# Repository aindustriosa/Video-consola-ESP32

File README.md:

# Videoconsola ESP32

Unha videoconsola portátil feita por nós, e un SDK para aprender a programar
os teus propios xogos nela.

## Que leva

- **XIAO ESP32-C3** (o cerebro)
- Pantalla a cor **ILI9341 de 2,4"** (240 x 320 puntos)
- Cruceta, botóns **A**, **B** e **MENU**
- Zumbador para facer sons
- Batería **LiPo** que se carga polo USB-C

## Que hai neste repositorio

| Carpeta | Contido |
|---|---|
| `lib/VideoConsola/` | O SDK: a librería para programar a consola |
| `lib/VideoConsola/examples/` | Exemplos, do máis sinxelo ao máis completo |
| `xogo/` | Aquí vai o teu programa |
| `docs/` | [Primeiros pasos](docs/primeiros-pasos.md) e [referencia do SDK](docs/referencia.md) |
| `hardware/` | [PCB (KiCad), esquema, lista de materiais e carcasa 3D](hardware/README.md) |

## Un programa en 10 liñas

```cpp
#include <VideoConsola.h>

void setup() {
  consola.iniciar();
  pantalla.texto_centrado("Ola, mundo!", 150, AMARELO);
}

void loop() {
  botons.ler();
  if (botons.acaba_de_premer(BOTON_A)) son.nota(DO, 200);
}
```

## Exemplos

| Exemplo | Que aprendes |
|---|---|
| `01_OlaMundo` | Escribir texto e números |
| `02_Formas` | Rectángulos, círculos, liñas, triángulos e cores |
| `03_Botons` | Ler os botóns |
| `04_Piano` | Notas e melodías |
| `05_Mover` | Mover algo pola pantalla |
| `06_Debuxos` | Facer personaxes con números e animalos |
| `07_Bola` | Un xogo completo con puntos e récord |
| `08_Serpe` | O xogo da serpe |

## Comezar

Le os [primeiros pasos](docs/primeiros-pasos.md). En resumo, con
[PlatformIO](https://platformio.org/):

```bash
pio run -t upload
```

Isto compila o programa da carpeta `xogo/` e gravao na consola.

## Licenza

Este traballo está suxeito á licenza [GNU General Public License v3.0](LICENSE).

Todos os ficheiros multimedia e de datos que non sexan código fonte están suxeitos á licenza
[Creative Commons Attribution-ShareAlike 4.0 (CC BY-SA 4.0)](LICENSE-CC-BY-SA-4.0.txt).

---

Esta actividade está patrocinada pola Xunta de Galicia e pola Axencia Para a Modernización Tecnolóxica (AMTEGA).

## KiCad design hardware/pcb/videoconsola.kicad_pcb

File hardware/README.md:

# Hardware

## Placa (PCB)

PCB dunha soa cara de 60 x 90 mm, pensada para fresar en CNC. Os botóns, o
zumbador e a pantalla van pola cara dianteira; o XIAO, o chip dos botóns e o
resto de compoñentes SMD, pola traseira (a do cobre).

| Cara dianteira | Cara traseira |
|---|---|
|  |  |

Ficheiros en `pcb/`:

- `videoconsola.kicad_pro`, `.kicad_sch`, `.kicad_pcb`: proxecto KiCad (versión 10)
- `esquema.pdf`: o esquema
- `gerber/`: Gerber e taladros, para fresar ou encargar a placa
- `lista_materiais.csv`: lista de materiais
- `videoconsola.step`: modelo 3D da placa

As resistencias de **0 ohm** fan de ponte para cruzar pistas (a placa só ten unha cara).

## Conexións

| XIAO | GPIO | Vai a |
|---|---|---|
| D0 | 2 | Batería, a través dun divisor 100k + 100k |
| D1 | 3 | INT do PCF8574A (pull-up 10k) |
| D2 | 4 | Zumbador, a través dun transistor MMBT3904 |
| D3 | 5 | Pantalla RESET |
| D4 | 6 | I2C SDA (pull-up 4k7) |
| D5 | 7 | I2C SCL (pull-up 4k7) |
| D6 | 21 | Pantalla D/C |
| D7 | 20 | Pantalla CS |
| D8 | 8 | Pantalla SCK |
| D9 | 9 | Acende a pantalla (MOSFET, nivel alto = acesa) |
| D10 | 10 | Pantalla MOSI |
| BAT+ / BAT- | | Batería LiPo (conector JST-PH) |

Botóns no PCF8574A (enderezo I2C `0x38`): P0 arriba, P1 abaixo, P2 esquerda,
P3 dereita, P4 B, P5 A, P6 MENU. Cada botón vai a GND.

## Lista de materiais

| Cant. | Compoñente | Referencias |
|---|---|---|
| 1 | Seeed Studio XIAO ESP32-C3 | M1 |
| 1 | Pantalla TFT 2,4" ILI9341 SPI, 240 x 320, módulo de 14 pins (MSP2402) | J2 |
| 1 | PCF8574A, SOIC-16 | U1 |
| 7 | Pulsador 6 x 6 x 5 mm, de patas | SW1-SW6, SW_MENU1 |
| 1 | Zumbador pasivo de 12 mm (CEM-1203) | BZ1 |
| 1 | Transistor NPN MMBT3904, SOT-23 | Q1 |
| 1 | MOSFET de canle N, SOT-23 | Q2 |
| 1 | Díodo 1N4148W | D1 |
| 2 | Condensador 100 nF, 1206 | C1, C2 |
| 2 | Resistencia 4k7, 1206 | R2, R3 |
| 3 | Resistencia 10k, 1206 | R4, R11, R16 |
| 2 | Resistencia 100k, 1206 | R8, R9 |
| 2 | Resistencia 1k, 1206 | R10, R17 |
| 7 | Resistencia 0 ohm, 1206 (pontes) | R5-R7, R12-R14, R18 |
| 1 | Conector JST-PH 2 pins, SMD horizontal | J_BAT1 |
| 1 | Batería LiPo 3,7 V 1800 mAh, 103450 (10 x 34 x 50 mm) con conector JST-PH | |
| 4 | Parafuso M3 x 25 de cabeza avellanada | |

## Carcasa

Carcasa en dúas metades, deseñada en OpenSCAD a partir das medidas da PCB.

| Fronte | Traseira (co oco da batería) |
|---|---|
|  |  |

Ficheiros en `carcasa/`:

- `fronte.stl`: a metade dianteira (ventá da pantalla, botóns e reixa do zumbador)
- `traseira.stl`: a tapa de atrás (oco para a batería e saída do USB-C)
- `botons.stl`: cruceta, A, B e MENU
- `carcasa.scad`: o deseño, con todas as medidas como parámetros

### Imprimir

- PLA ou PETG, capa de 0,2 mm.
- `fronte.stl` coa cara de fóra apoiada na cama.
- `traseira.stl` co fondo apoiado na cama.
- `botons.stl` tal como está (a cara de arriba dos botóns apoiada na cama).

### Montar

1. Solda a pantalla directamente na PCB, co separador de plástico dos pins.
2. Pon os botóns no seu sitio na fronte e encaixa a PCB enriba
   (a cruceta ten un pivote que entra no furado de 6 mm da placa).
3. Conecta a batería e déitaa no seu oco da traseira.
4. Pecha cos 4 parafusos M3 x 25 desde atrás.

### Axustar

Se a túa pantalla, batería ou botóns son diferentes, cambia as medidas ao
principio de `carcasa.scad` e volve exportar os STL:

```bash
openscad -D 'parte="fronte"'   -o fronte.stl   carcasa.scad
openscad -D 'parte="traseira"' -o traseira.stl carcasa.scad
openscad -D 'parte="botons"'   -o botons.stl   carcasa.scad
```

Con `parte="montaxe"` vese todo montado xunto coa electrónica, para revisar.

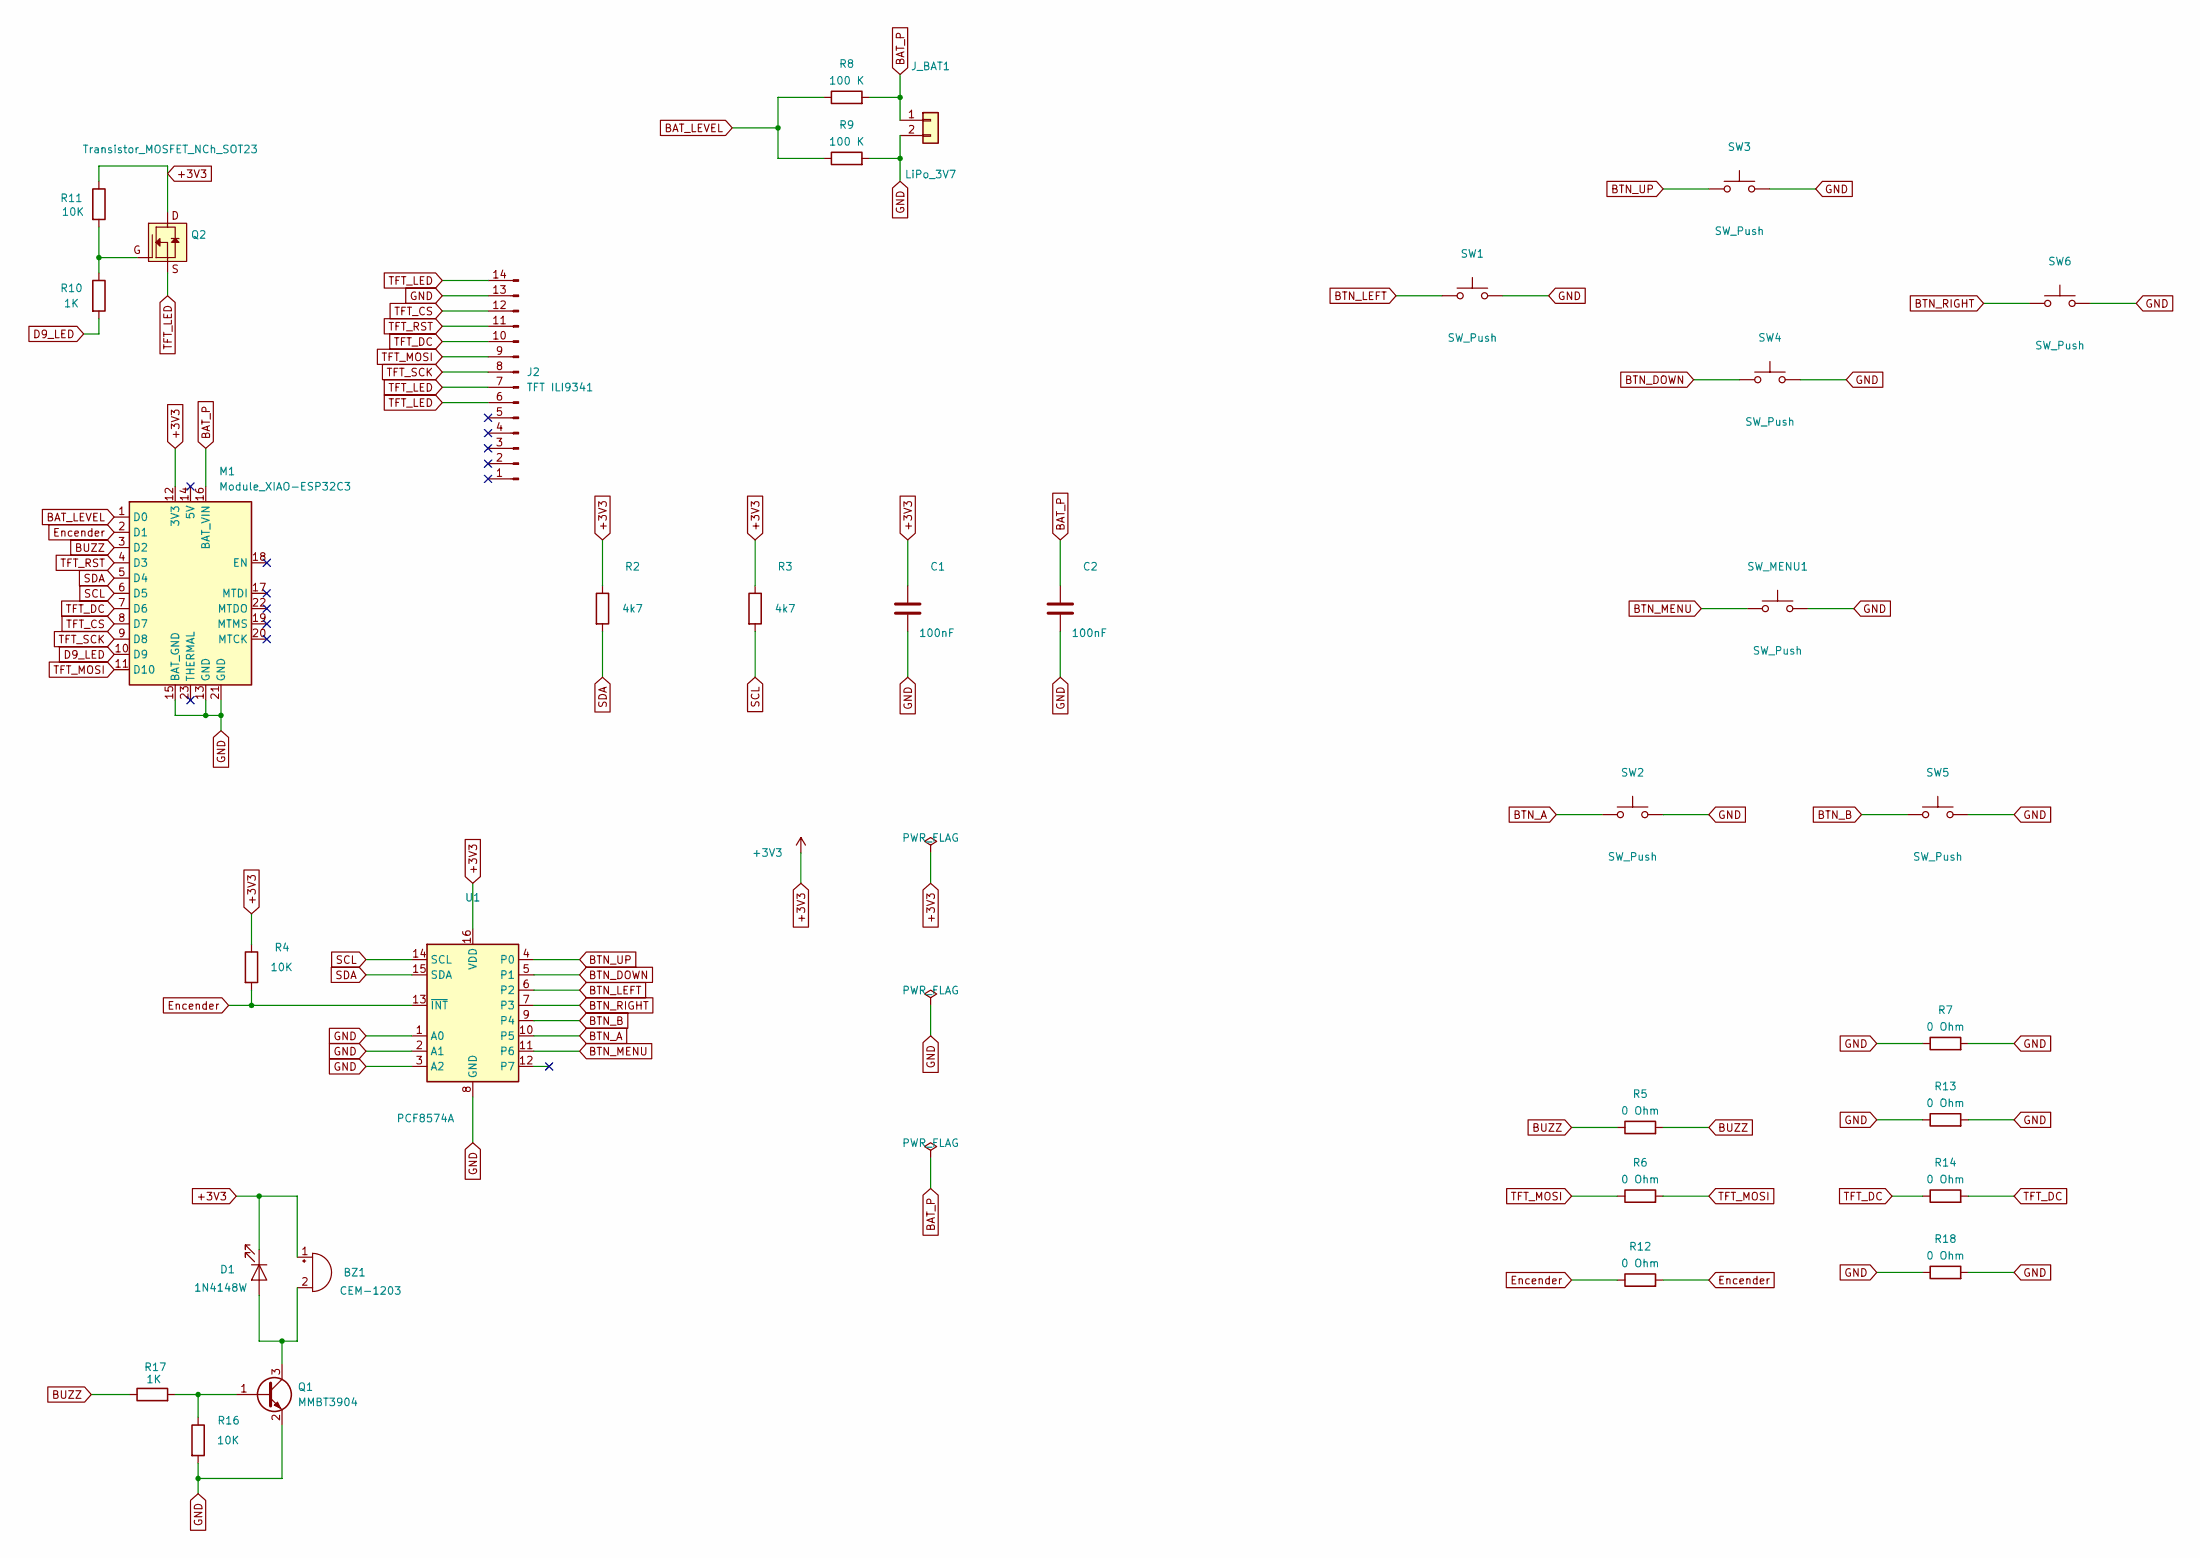
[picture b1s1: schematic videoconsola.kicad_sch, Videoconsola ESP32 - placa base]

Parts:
BZ1: CEM-1203; MagneticBuzzer_ProSignal_ABT-410-RC
C1, C2: 100nF; C_1206
D1: 1N4148W; LED_1206
J2: TFT ILI9341; PinHeader_1x14_P2.54mm_Vertical
J_BAT1: LiPo_3V7; JST_PH_S2B-PH-SM4-TB_1x02-1MP_P2.00mm_Horizontal
M1: Module_XIAO-ESP32C3; SeeedStudio_XIAO_ESP32C3
Q1: MMBT3904; SOT-23
Q2: Transistor_MOSFET_NCh_SOT23; SOT-23-3
R2, R3: 4k7; R_1206
R4, R11, R16: 10K; R_1206
R5, R6, R7, R12, R13, R14, R18: 0 Ohm; R_1206
R8, R9: 100 K; R_1206
R10, R17: 1K; R_1206
SW1, SW2, SW3, SW4, SW5, SW6: SW_Push; SW_PUSH_6mm
SW_MENU1: SW_Push; SW_PUSH_6mm
U1: PCF8574A; SOIC-16W_7.5x10.3mm_P1.27mm

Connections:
+3V3: BZ1.1 (+), C1.1, D1.1 (K), M1.12 (3V3), Q2.3 (D), R2.1, R3.1, R4.1, R11.1, U1.16 (VDD)
BAT_LEVEL: M1.1 (D0), R8.1, R9.1
BAT_P: C2.1, J_BAT1.1, M1.16 (BAT_VIN), R8.2
BTN_A: SW2.1, U1.10 (P5)
BTN_B: SW5.1, U1.9 (P4)
BTN_DOWN: SW4.1, U1.5 (P1)
BTN_LEFT: SW1.1, U1.6 (P2)
BTN_MENU: SW_MENU1.1, U1.11 (P6)
BTN_RIGHT: SW6.1, U1.7 (P3)
BTN_UP: SW3.1, U1.4 (P0)
BUZZ: M1.3 (D2), R5.1, R5.2, R17.1
D9_LED: M1.10 (D9), R10.2
Encender: M1.2 (D1), R4.2, R12.1, R12.2, U1.13 (~INT)
GND: C1.2, C2.2, J2.13, J_BAT1.2, M1.13 (GND), M1.15 (BAT_GND), M1.21 (GND), Q1.2 (E), R7.1, R7.2, R9.2, R13.1, R13.2, R16.2, R18.1, R18.2, SW1.2, SW2.2, SW3.2, SW4.2, SW5.2, SW6.2, SW_MENU1.2, U1.1 (A0), U1.2 (A1), U1.3 (A2), U1.8 (GND)
unnamed: BZ1.2 (-), D1.2 (A), Q1.3 (C)
unnamed: Q1.1 (B), R16.1, R17.2
unnamed: Q2.1 (G), R10.1, R11.2
SCL: M1.6 (D5), R3.2, U1.14 (SCL)
SDA: M1.5 (D4), R2.2, U1.15 (SDA)
TFT_CS: J2.12, M1.8 (D7)
TFT_DC: J2.10, M1.7 (D6), R14.1, R14.2
TFT_LED: J2.6, J2.7, J2.14, Q2.2 (S)
TFT_MOSI: J2.9, M1.11 (D10), R6.1, R6.2
TFT_RST: J2.11, M1.4 (D3)
TFT_SCK: J2.8, M1.9 (D8)

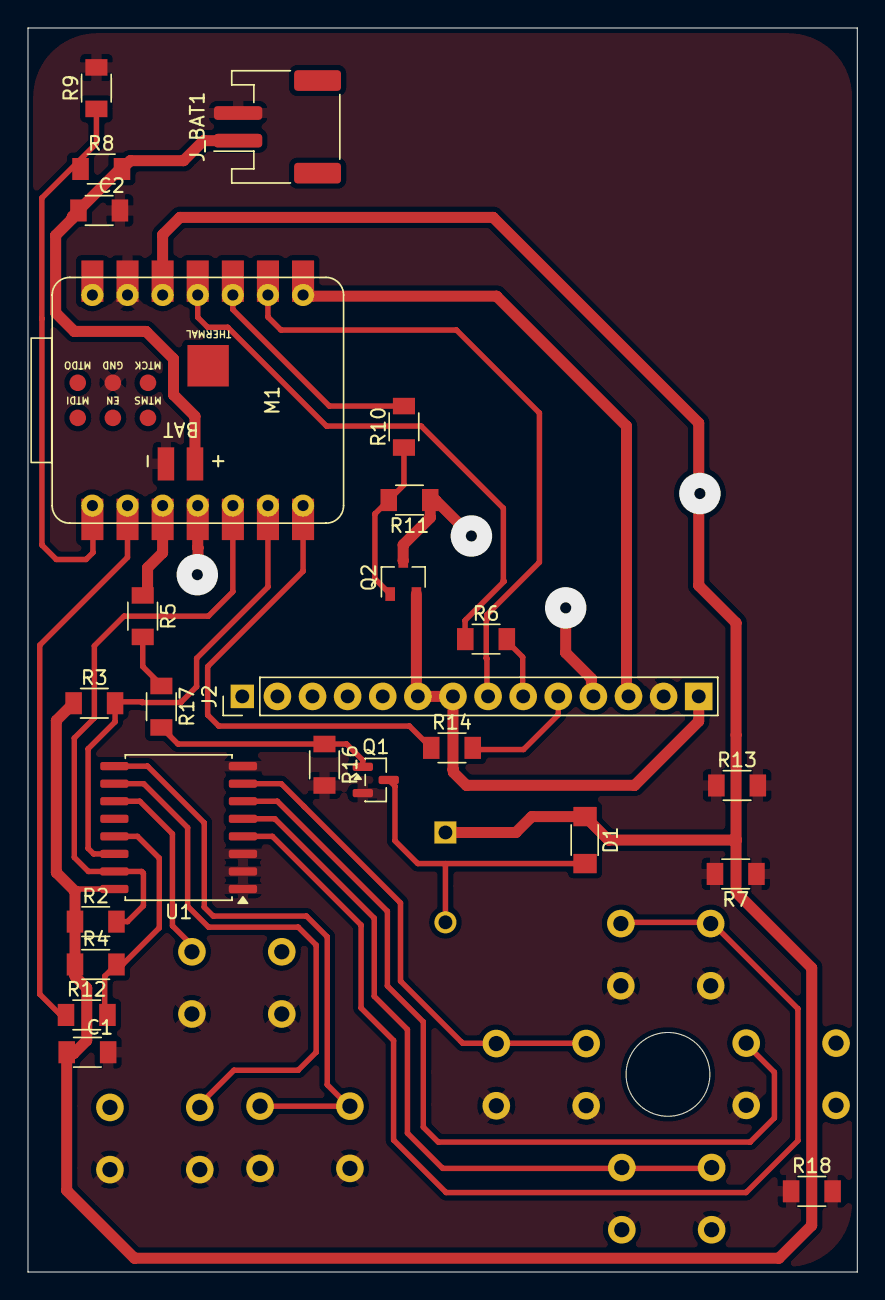
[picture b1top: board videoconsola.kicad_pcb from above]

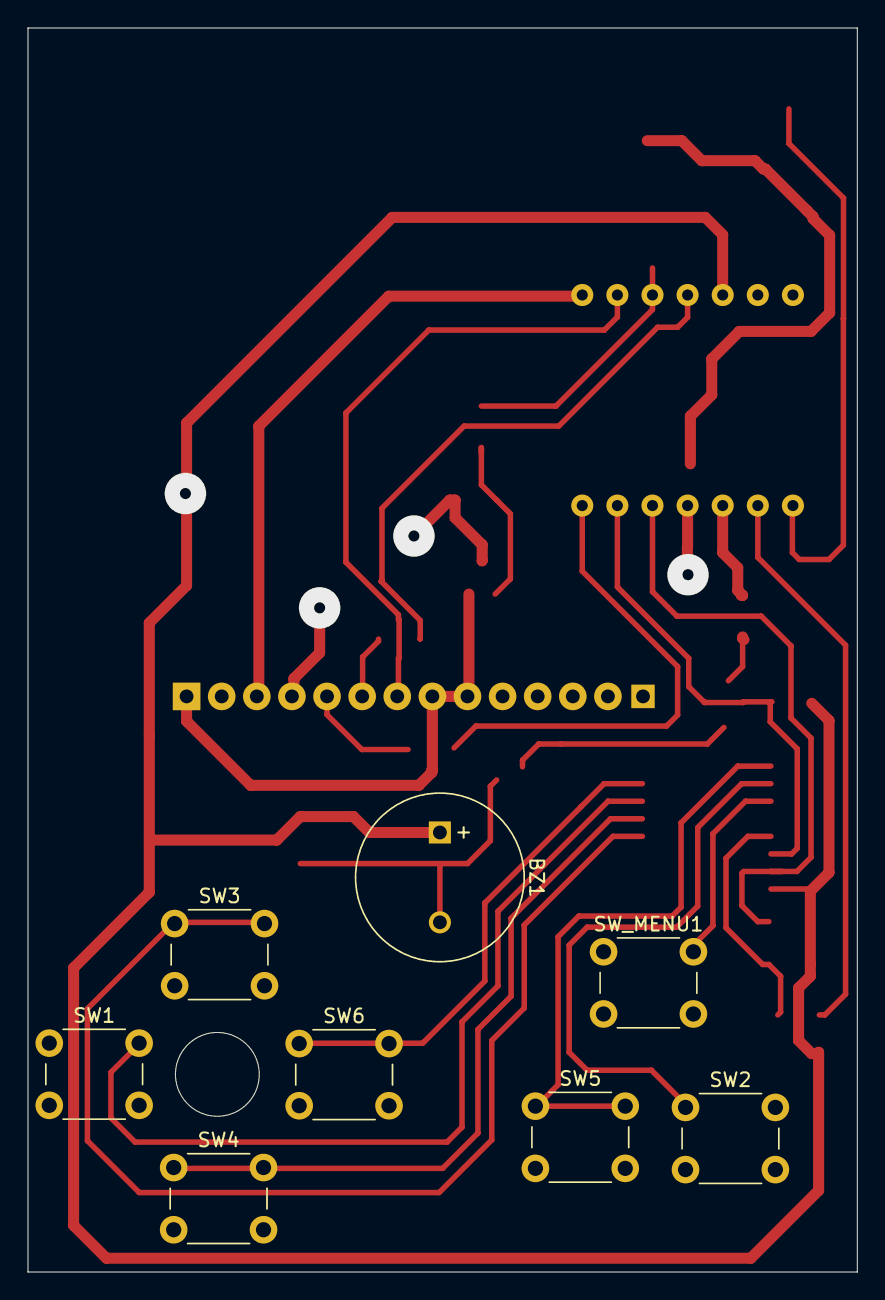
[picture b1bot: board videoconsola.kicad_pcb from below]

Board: 2 copper layers, 60.0 x 90.0 mm, 33 parts (8 on the bottom side), 25 nets.
